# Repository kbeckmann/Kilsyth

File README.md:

# WIP! WIP! WIP! 
This repo is a work in progress and far from release-worthy. Please don't make your own boards and expect any kind of support. However, it might reach a stable point sometime in the future (as of 2019-01).

# Kilsyth: ECP5 FPGA + FT60x FIFO
Kilsyth is a piece of hardware that contains an FPGA (Lattice ECP5) and a SuperSpeed USB 3.0 FIFO-bridge (FT60x). The goal is to provide a platform to be able to transfer high speed data transfers between a PC and an FPGA. The FPGA in turn can do whatever - e.g. interface with SDR, video capture, act as a logic analyzer.

## Current status
It's still in the early bring-up phase. Initial verification shows that it actually seems to work.

### RevA
RevA is the first prototype and has been designed and built.

- [x] It doesn't smoke when powered up.
- [x] USB-C connector works but is messy to solder.
- [ ] Loopback test is almost in place. Using the proprietary driver, high bi-directional speeds are achieavable (> 98MB/s in both directions simultaneously). Just need to figure out some off-by-one errors...
- [ ] Bootloader to store a custom bitstream on the flash.

Errata:
- C9 is not a GPIO on ECP5 F12 and some other variants. To get the LED working put a jumper on pin 31 and 33 on the Wide connector.
- FT_CLK is not routed to a clock pin. Can be fixed with a bodge wire! Remove R50 and R36, swap their paths.
- JTAG connector has a funky footprint on the PCB because CCW vs Odd/Even pinout on the symbol vs footprint. But the PCB silk screen is accurate so don't worry - it's just a stupid pinout.
- Need to add pull-ups for the SPI flash.

### RevB
Ideas for RevB are still being collected. Feel free to suggest changes in an issue.

- Add support for reversible USB-C connector using [PI5USB30213A](https://www.diodes.com/products/connectivity-and-timing/switches-mux/protocol-switches/usb-switches/part/PI5USB30213A).

## Software usage (TODO)

Requires a patched migen and a patched ftdi library.. Nasty, I know, sorry.

```
Help:
$ python -m software.kilsyth -h

Run blinky:
$ python -m software.kilsyth run blinky

```

# Contact

Reach out to [@kbeckmann](https://twitter.com/kbeckmann) on Twitter or IRC/Freenode.

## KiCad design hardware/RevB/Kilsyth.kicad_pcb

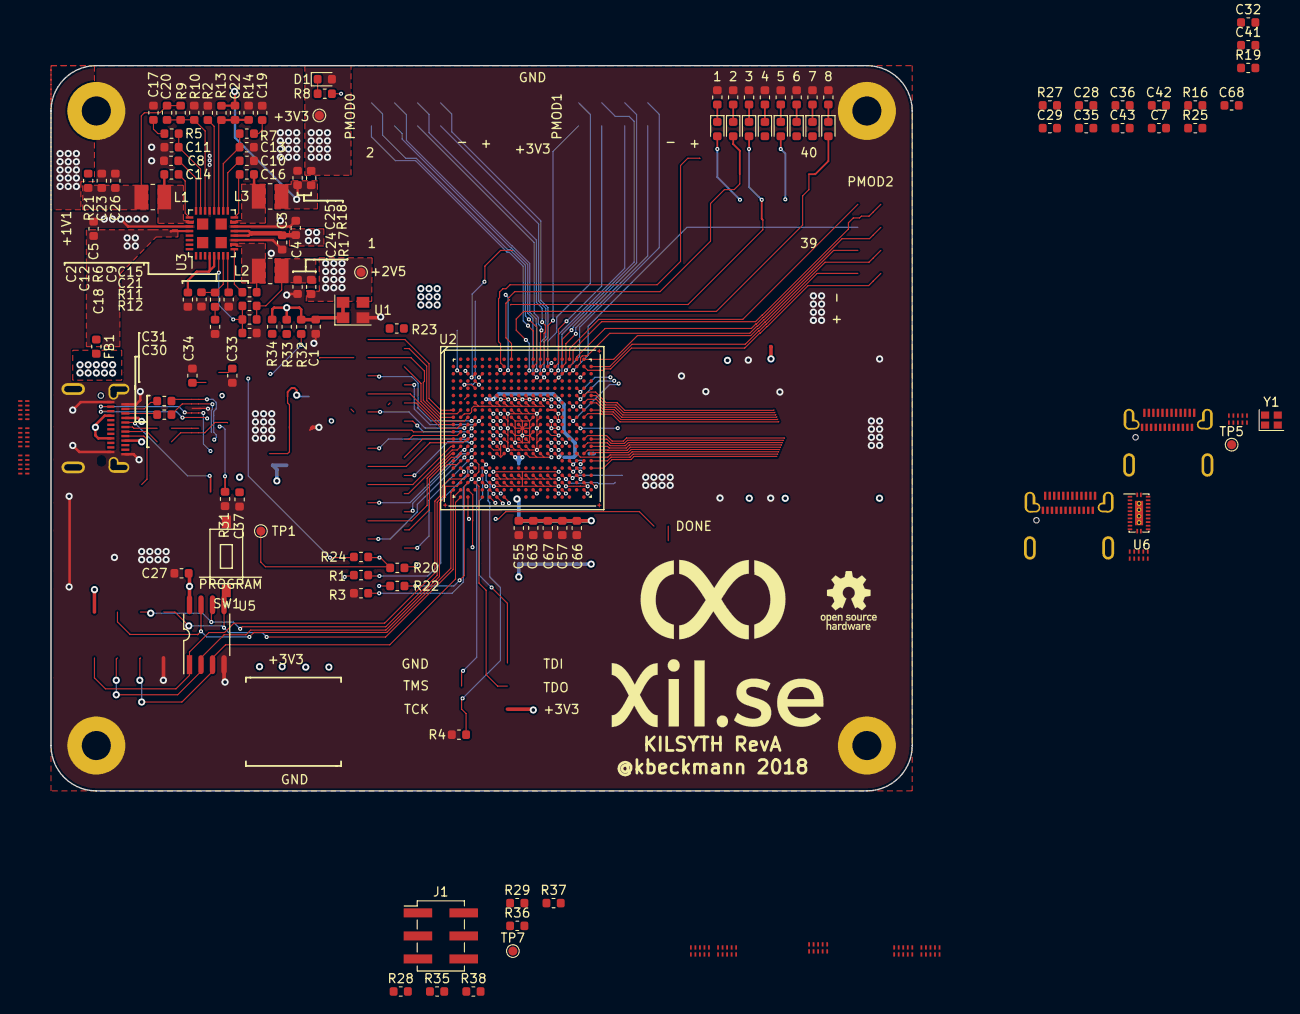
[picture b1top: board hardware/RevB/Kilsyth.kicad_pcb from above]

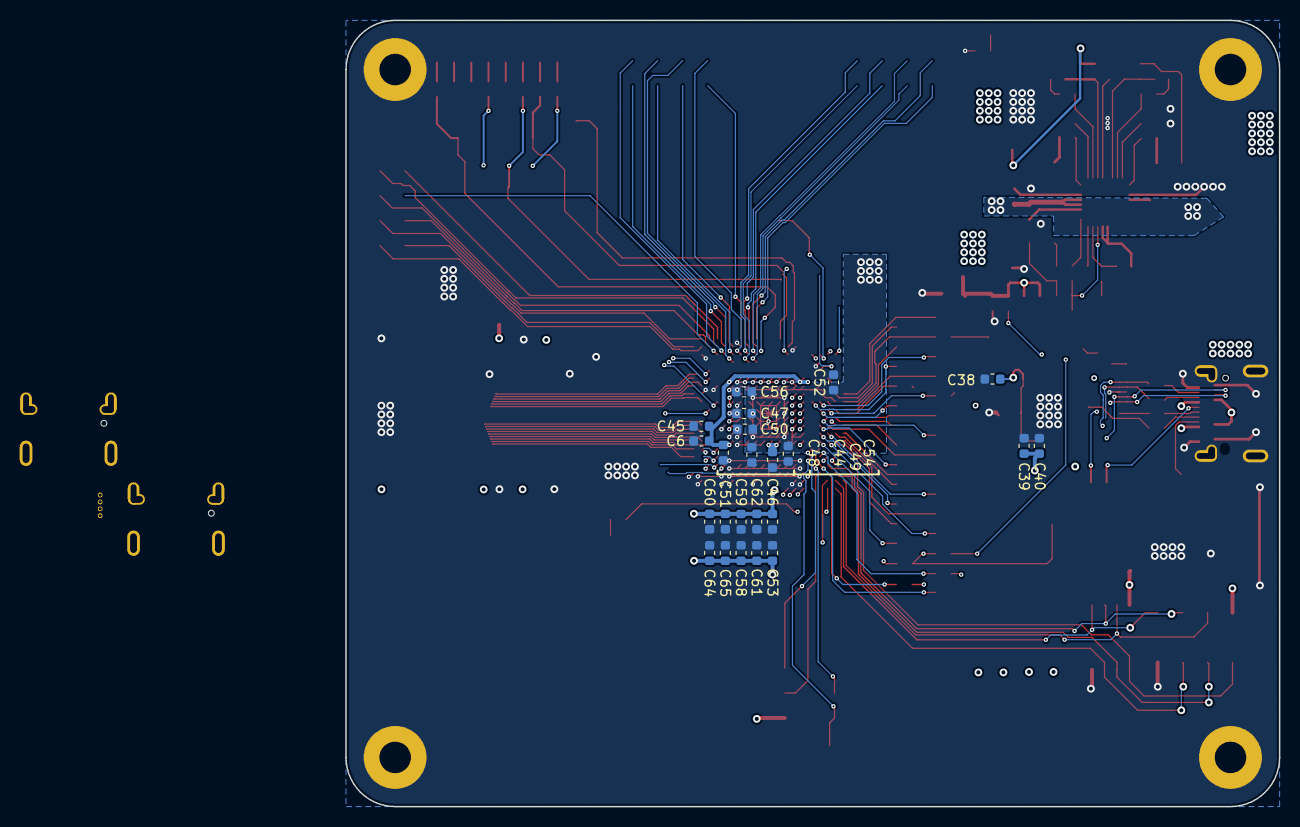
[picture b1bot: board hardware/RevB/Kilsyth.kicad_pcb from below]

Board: 4 copper layers, 95.0 x 80.0 mm, 154 parts (23 on the bottom side), 112 nets.

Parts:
C1, C6, C7, C27, C28, C29, C30, C31, C32, C35, C36, C37, C39, C40, C41, C42, C43, C44, C45, C46, C50, C51, C54, C55, C58, C60, C62, C64, C66, C68: 100n; C_0603_1608Metric
C2: 1u; C_0603_1608Metric
C3, C4, C5: 10u; C_0603_1608Metric
C8, C9, C10, C47, C48, C49, C52, C53, C56, C57, C59, C61, C63, C65, C67: 10n; C_0603_1608Metric
C11, C12, C13, C20, C21, C22: 22p; C_0603_1608Metric
C14, C15, C16: 47n; C_0603_1608Metric
C17, C18, C19: 3.3n; C_0603_1608Metric
C23, C24, C25, C26: 22u; C_0603_1608Metric
C33, C34: 18p; C_0603_1608Metric
C38: 4u7; C_0603_1608Metric
D1, D3, D4, D5, D6, D7, D8, D9, D10: LED; LED_0603_1608Metric
FB1: Ferrite_Bead; L_0603_1608Metric
H1, H2, H3, H4: MountingHole_3.2mm_M3_Pad
J1: Conn_JTAG; PinHeader_2x03_P2.54mm_Vertical_SMD
J2, J6, J7: DX07S024JJ2; USBC_DX07S024JJ2R1300
J3, J4, J5, J8, J9, J10, J11, J12, J13, J14: PUSB3FR4Z
L1, L2, L3: 2.2u; L_1008_1210
R1, R3, R12: 4.7K; R_0603_1608Metric
R2: 73.2K; R_0603_1608Metric
R4, R28: 4k7; R_0603_1608Metric
R5, R6, R7: 20K; R_0603_1608Metric
R8, R15, R26, R30, R59, R60, R61, R62, R63: 2K; R_0603_1608Metric
R9, R11, R13: 15K; R_0603_1608Metric
R10: 7K5; R_0603_1608Metric
R14: 3.3K; R_0603_1608Metric
R16, R27: 910K; R_0603_1608Metric
R17, R18, R21, R23, R24: 0R; R_0603_1608Metric
R19, R25: 2K2; R_0603_1608Metric
R20, R22, R32, R33, R34: 10K; R_0603_1608Metric
R29, R35, R37, R38: 10k; R_0603_1608Metric
R31: 1K6; R_0603_1608Metric
R36: 1k1; R_0603_1608Metric
SW1: SW_Push; SmallButton
TP1, TP2, TP3, TP5, TP7: TestPoint; TestPoint_Pad_D1.0mm
U1: DSC6001CI2A-016.0000T; Crystal_SMD_3225-4Pin_3.2x2.5mm
U2: LFE5UM-45F-6BG381C; BGA-381_pitch0.8mm_dia0.4mm
U3: TPS65261; S-PVQFN-N32
U5: IS25LP128F-JBLE; SOA008-150-208mil
U6: PI5USB30213A
Y1: 30MHz ±20ppm; Crystal_SMD_2016-4Pin_2.0x1.6mm

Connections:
+1V1: C44.1, C47.1, C50.1, C52.1, C54.1, C56.1, U2.H8, U2.H9, U2.H10, U2.H11, U2.H12, U2.H13, U2.J8, U2.J13, U2.K8, U2.K13, U2.L8, U2.L13, U2.M8, U2.M13, U2.N8, U2.N9, U2.N10, U2.N11, U2.N12, U2.N13
+1V8: R21.1, TP5.1
+2V5: C6.1, C45.1, C48.1, R17.1, TP2.1, U2.F6, U2.F15, U2.P6, U2.P15
+3V3: C1.1, C27.1, C39.1, C40.1, C46.1, C49.1, C51.1, C53.1, C55.1, C57.1, C58.1, C59.1, C60.1, C61.1, C62.1, C63.1, C64.1, C65.1, C66.1, C67.1, D1.2, J1.2, R1.1, R18.1, R19.2, R20.2, R22.2, R25.2, R28.1, R29.1, R32.2, R33.2, R34.2, R35.1, R36.1, R37.1, R38.1, TP3.1, U1.1, U1.4, U2.F9, U2.F10, U2.F11, U2.F12, U2.H6, U2.H7, U2.H14, U2.H15, U2.J6, U2.J15, U2.L6, U2.L7, U2.L14, U2.L15, U2.M6, U2.M15, U2.P9, U2.P10, U2.T2, U2.T3, U2.U2, U5.8
+5V: C3.1, C4.1, C5.1, J6.A4, J6.A9, J6.B4, J6.B9, J7.A4, J7.A9, J7.B4, J7.B9, U3.12, U3.13, U3.28, U3.29
/CC1: J2.A5, J4.5, J4.6, U6.11
/CC2: J2.B5, J4.4, J4.7, U6.12
/FLASH_CSn: R28.2, U2.R2, U5.1
/FLASH_HOLDn: R29.2, U2.W1, U5.7
/FLASH_MISO: R38.2, U2.V2, U5.2
/FLASH_MOSI: R37.2, U2.W2, U5.5
/FLASH_SCK: R36.2, U2.U3, U5.6
/FLASH_WPn: R35.2, U2.Y2, U5.3
/HDRX0_D0CH0_N: J6.B10, J8.5, J8.6, U2.Y6
/HDRX0_D0CH0_P: J6.B11, J8.4, J8.7, U2.Y5
/HDRX0_D0CH1_N: J6.A10, J9.5, J9.6, U2.Y8
/HDRX0_D0CH1_P: J6.A11, J9.4, J9.7, U2.Y7
/HDRX0_D1CH0_N: J7.B10, J11.5, J11.6, U2.Y15
/HDRX0_D1CH0_P: J7.B11, J11.4, J11.7, U2.Y14
/HDRX0_D1CH1_N: J7.A10, J12.5, J12.6, U2.Y17
/HDRX0_D1CH1_P: J7.A11, J12.4, J12.7, U2.Y16
/HDTX0_D0CH0_N: C29.2, J8.2, J8.9, U2.W5
/HDTX0_D0CH0_P: C32.2, J8.1, J8.10, U2.W4
/HDTX0_D0CH1_N: C35.2, J9.2, J9.9, U2.W9
/HDTX0_D0CH1_P: C36.2, J9.1, J9.10, U2.W8
/HDTX0_D1CH0_N: C41.2, J11.2, J11.9, U2.W14
/HDTX0_D1CH0_P: C42.2, J11.1, J11.10, U2.W13
/HDTX0_D1CH1_N: C43.2, J12.2, J12.9, U2.W18
/HDTX0_D1CH1_P: C68.2, J12.1, J12.10, U2.W17
/INITn: R22.1, U2.V3
/JTAG_TCK: J1.4, R4.1, U2.T5
/JTAG_TDI: J1.3, U2.R5
/JTAG_TDO: J1.6, U2.V4
/JTAG_TMS: J1.5, U2.U5
/REFCLK_D0_N: J6.B8, J10.4, J10.7, U2.Y12
/REFCLK_D0_P: J6.A8, J10.5, J10.6, U2.Y11
/REFCLK_D1_N: J7.B8, J10.1, J10.10, U2.W20
/REFCLK_D1_P: J7.A8, J10.2, J10.9, U2.Y19
/RX1+: J2.B11, J3.5, J3.6, U6.14
/RX1-: J2.B10, J3.4, J3.7, U6.15
/RX2+: J2.A11, J5.4, J5.7, U6.19
/RX2-: J2.A10, J5.5, J5.6, U6.18
/TX1+: C31.1, J2.A2, J3.2, J3.9
/TX1-: C30.1, J2.A3, J3.1, J3.10
/TX2+: C28.1, J2.B2, J5.1, J5.10
/TX2-: C7.1, J2.B3, J5.2, J5.9
/USBC0_CC1: J6.A5, J13.5, J13.6
/USBC0_CC2: J6.B5, J13.4, J13.7
/USBC0_USB_N: J6.A7, J6.B7, J13.2, J13.9
/USBC0_USB_P: J6.A6, J6.B6, J13.1, J13.10
/USBC1_CC1: J7.A5, J14.5, J14.6
/USBC1_CC2: J7.B5, J14.4, J14.7
/USBC1_USB_N: J7.A7, J7.B7, J14.2, J14.9
/USBC1_USB_P: J7.A6, J7.B6, J14.1, J14.10
/USB_D+: J2.A6, J2.B6, J4.2, J4.9
/USB_D-: J2.A7, J2.B7, J4.1, J4.10
FT_GPIO0: R20.1, R24.2, R25.1, SW1.2, TP1.1, U2.W3
FT_GPIO1: R19.1, R23.2
GND: C1.2, C2.2, C3.2, C4.2, C5.2, C6.2, C8.2, C9.2, C10.2, C11.2, C12.2, C13.2, C17.2, C18.2, C19.2, C23.2, C24.2, C25.2, C26.2, C27.2, C33.1, C34.1, C37.2, C38.2, C39.2, C40.2, C44.2, C45.2, C46.2, C47.2, C48.2, C49.2, C50.2, C51.2, C52.2, C53.2, C54.2, C55.2, C56.2, C57.2, C58.2, C59.2, C60.2, C61.2, C62.2, C63.2, C64.2, C65.2, C66.2, C67.2, H1.1, H2.1, H3.1, H4.1, J1.1, J2.A1, J2.A12, J2.B1, J2.B12, J2.S1, J3.3, J3.8, J4.3, J4.8, J5.3, J5.8, J6.A1, J6.A12, J6.B1, J6.B12, J6.S1, J7.A1, J7.A12, J7.B1, J7.B12, J7.S1, J8.3, J8.8, J9.3, J9.8, J10.3, J10.8, J11.3, J11.8, J12.3, J12.8, J13.3, J13.8, J14.3, J14.8, R2.2, R3.1, R4.2, R8.2, R10.2, R12.2, R14.2, R15.2, R26.2, R30.2, R31.2, R59.2, R60.2, R61.2, R62.2, R63.2, SW1.1, U1.2, U2.B7, U2.B14, U2.C19, U2.D4, U2.F7, U2.F8, U2.F13, U2.F14, U2.G4, U2.G6, U2.G7, U2.G8, U2.G9, U2.G10, U2.G11, U2.G12, U2.G13, U2.G14, U2.G15, U2.G17, U2.H19, U2.J2, U2.J7, U2.J9, U2.J10, U2.J11, U2.J12, U2.J14, U2.K6, U2.K7, U2.K9, U2.K10, U2.K11, U2.K12, U2.K14, U2.K15, U2.L9, U2.L10, U2.L11, U2.L12, U2.M2, U2.M7, U2.M9, U2.M10, U2.M11, U2.M12, U2.M14, U2.M16, U2.N6, U2.N7, U2.N14, U2.N15, U2.P7, U2.P8, U2.P11, U2.P12, U2.P13, U2.P14, U2.R19, U2.U7, U2.U8, U2.U9, U2.U10, U2.U11, U2.U12, U2.U13, U2.U14, U2.V5, U2.V6, U2.V7, U2.V8, U2.V9, U2.V12, U2.V13, U2.V14, U2.V15, U2.V16, U2.V19, U2.V20, U2.W6, U2.W7, U2.W12, U2.W15, U2.W16, U2.W19, U3.11, U3.14, U3.21, U3.27, U5.4, U6.3, U6.13, U6.PAD
unnamed: C2.1, U3.4, U3.5
unnamed: C7.2, U6.20
unnamed: C8.1, U3.24
unnamed: C9.1, U3.8
unnamed: C10.1, U3.17
unnamed: C11.1, R5.1, U3.23
unnamed: C12.1, R6.1, U3.7
unnamed: C13.1, R7.1, U3.18
unnamed: C14.1, U3.25
unnamed: C14.2, L1.1, U3.26
unnamed: C15.1, U3.9
unnamed: C15.2, L2.1, U3.10
unnamed: C16.1, U3.16
unnamed: C16.2, L3.1, U3.15
unnamed: C17.1, R5.2
unnamed: C18.1, R6.2
unnamed: C19.1, R7.2
unnamed: C20.1, C23.1, C26.1, L1.2, R9.1, R21.2
unnamed: C20.2, R9.2, R10.1, U3.22
unnamed: C21.1, C24.1, L2.2, R11.1, R17.2
unnamed: C21.2, R11.2, R12.1, U3.6
unnamed: C22.1, C25.1, L3.2, R13.1, R18.2
unnamed: C22.2, R13.2, R14.1, U3.19
unnamed: C28.2, U6.21
unnamed: C29.1, J6.A3
unnamed: C30.2, U6.17
unnamed: C31.2, U6.16
unnamed: C32.1, J6.A2
unnamed: C33.2, Y1.1
unnamed: C34.2, Y1.3
unnamed: C35.1, J6.B3
unnamed: C36.1, J6.B2
unnamed: C41.1, J7.A3
unnamed: C42.1, J7.A2
unnamed: C43.1, J7.B3
unnamed: C68.1, J7.B2
unnamed: D1.1, R8.1
unnamed: D3.1, R15.1
unnamed: D4.1, R26.1
unnamed: D5.1, R30.1
unnamed: D6.1, R59.1
unnamed: D7.1, R60.1
unnamed: D8.1, R61.1
unnamed: D9.1, R62.1
unnamed: D10.1, R63.1
unnamed: FB1.2, J2.A4, J2.A9, J2.B4, J2.B9
unnamed: R1.2, U2.T4
unnamed: R2.1, U3.20
unnamed: R3.2, U2.R4, U2.U4
unnamed: R16.2, U6.23
unnamed: TP7.1, U2.Y3
VBUS: FB1.1, R16.1, R27.2, U6.6
VD10: C37.1, C38.1

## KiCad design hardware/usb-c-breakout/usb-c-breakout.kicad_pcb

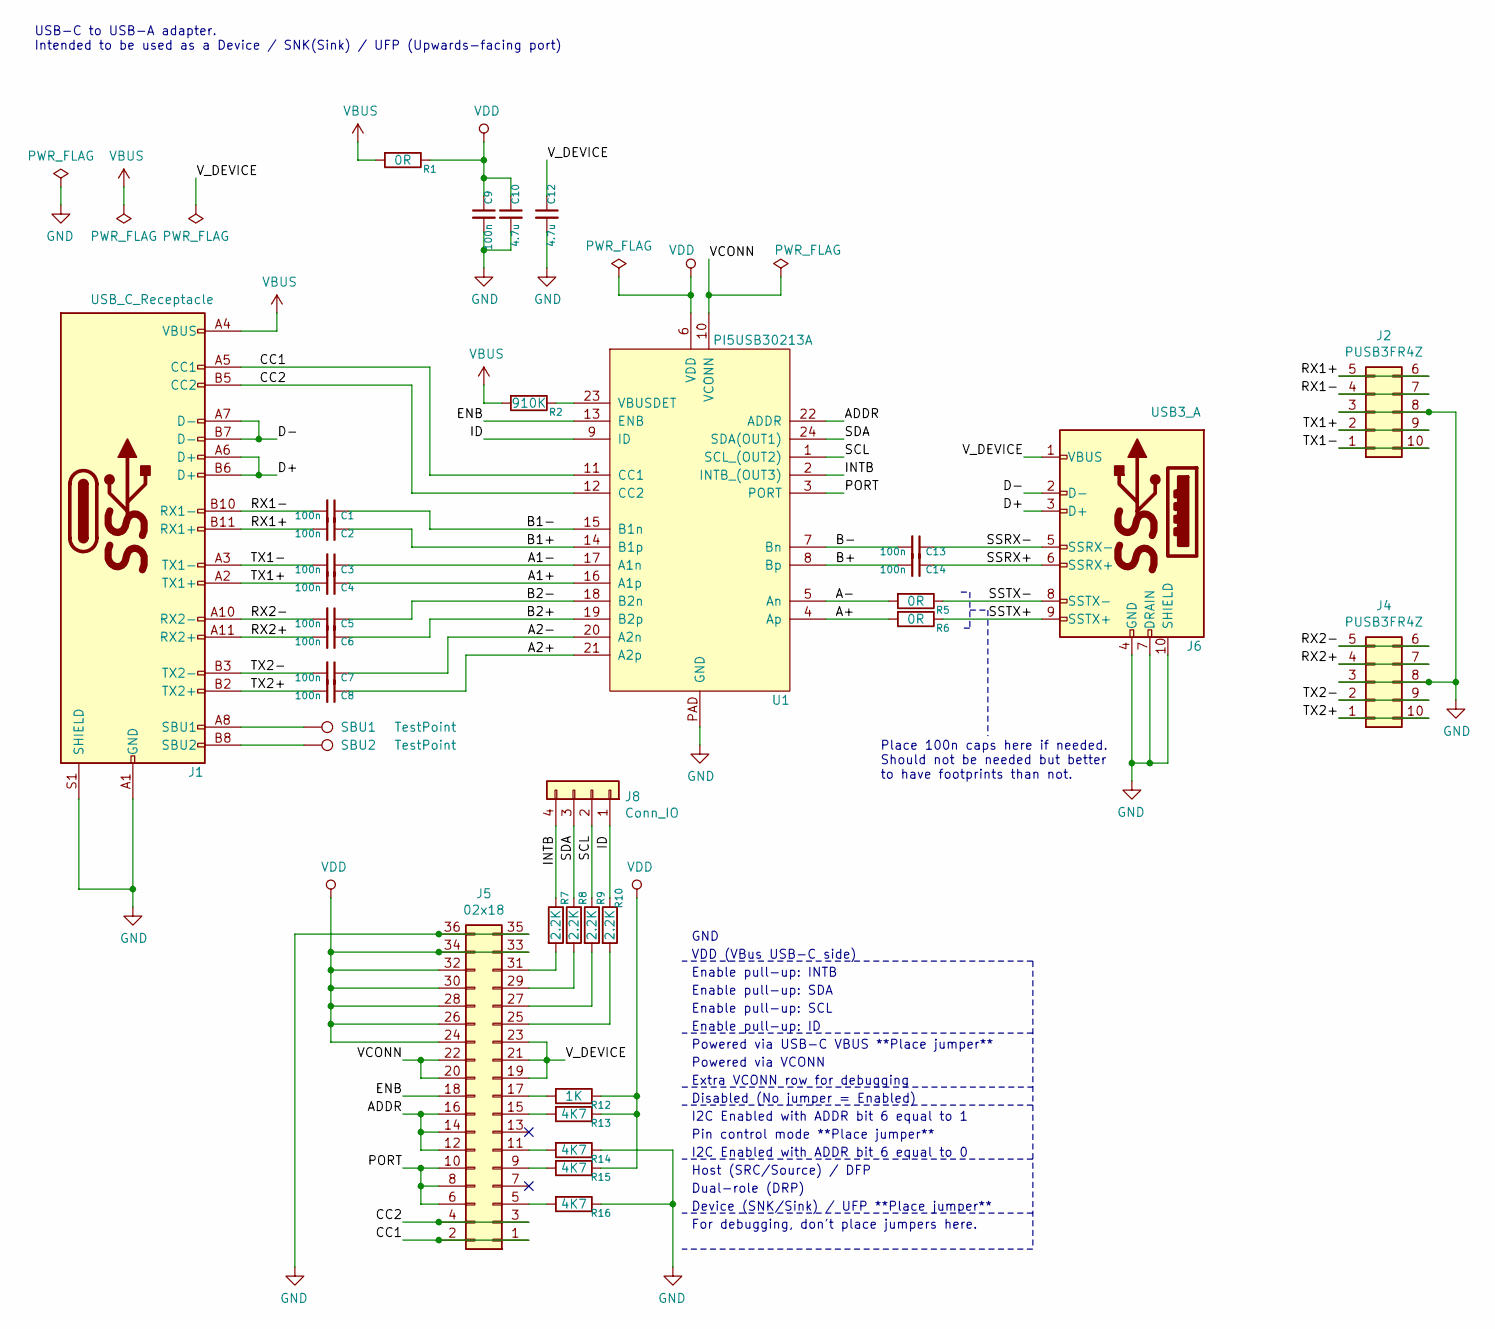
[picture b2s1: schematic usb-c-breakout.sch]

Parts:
C1, C2, C3, C4, C5, C6, C7, C8, C9, C13, C14: 100n; C_0402_1005Metric
C10, C12: 4.7u; C_0603_1608Metric
J1: USB_C_Receptacle; USB_C_Receptacle_CUI_UJ31-CH-31-SMT-TR
J2, J4: PUSB3FR4Z; Mouser 771-PUSB3FR4Z
J5: 02x18; PinHeader_2x18_P2.54mm_Vertical
J6: USB3_A; USB3_A_Female_Vertical
J8: Conn_IO; PinHeader_1x04_P2.54mm_Vertical
R1: 0R; R_0603_1608Metric
R2: 910K; R_0402_1005Metric
R5, R6: 0R; R_0402_1005Metric
R7, R8, R9, R10: 2.2K; R_0402_1005Metric
R12: 1K; R_0402_1005Metric
R13, R14, R15, R16: 4K7; R_0402_1005Metric
SBU1, SBU2: TestPoint; TestPoint_Pad_D1.0mm
U1: PI5USB30213A; Mouser PI5USB30213AXEAEX

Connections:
/A1+: C4.1, U1.16 (A1p)
/A1-: C3.1, U1.17 (A1n)
/A2+: C8.1, U1.21 (A2p)
/A2-: C7.1, U1.20 (A2n)
/A+: R6.2, U1.4 (Ap)
/A-: R5.2, U1.5 (An)
/ADDR: J5.12, J5.14, J5.16, U1.22 (ADDR)
/B1+: C2.1, U1.14 (B1p)
/B1-: C1.1, U1.15 (B1n)
/B2+: C6.1, U1.19 (B2p)
/B2-: C5.1, U1.18 (B2n)
/B+: C14.2, U1.8 (Bp)
/B-: C13.2, U1.7 (Bn)
/CC1: J1.A5 (CC1), J5.1, J5.2, U1.11 (CC1)
/CC2: J1.B5 (CC2), J5.3, J5.4, U1.12 (CC2)
/D+: J1.A6 (D+), J1.B6 (D+), J6.3 (D+)
/D-: J1.A7 (D-), J1.B7 (D-), J6.2 (D-)
/ENB: J5.18, U1.13 (ENB)
/ID: J8.1, R10.1, U1.9 (ID)
/INTB: J8.4, R7.1, U1.2 (INTB_(OUT3))
/PORT: J5.6, J5.8, J5.10, U1.3 (PORT)
/RX1+: C2.2, J1.B11 (RX1+), J2.5, J2.6
/RX1-: C1.2, J1.B10 (RX1-), J2.4, J2.7
/RX2+: C6.2, J1.A11 (RX2+), J4.4, J4.7
/RX2-: C5.2, J1.A10 (RX2-), J4.5, J4.6
/SCL: J8.2, R9.1, U1.1 (SCL_(OUT2))
/SDA: J8.3, R8.1, U1.24 (SDA(OUT1))
/SSRX+: C14.1, J6.6 (SSRX+)
/SSRX-: C13.1, J6.5 (SSRX-)
/SSTX+: J6.9 (SSTX+), R6.1
/SSTX-: J6.8 (SSTX-), R5.1
/TX1+: C4.2, J1.A2 (TX1+), J2.2, J2.9
/TX1-: C3.2, J1.A3 (TX1-), J2.1, J2.10
/TX2+: C8.2, J1.B2 (TX2+), J4.1, J4.10
/TX2-: C7.2, J1.B3 (TX2-), J4.2, J4.9
/VCONN: J5.20, J5.22, U1.10 (VCONN)
/V_DEVICE: C12.1, J5.19, J5.21, J5.23, J6.1 (VBUS)
GND: C9.2, C10.2, C12.2, J1.A1 (GND), J1.A12 (GND), J1.B1 (GND), J1.B12 (GND), J1.S1 (SHIELD), J2.3, J2.8, J4.3, J4.8, J5.35, J5.36, J6.4 (GND), J6.7 (DRAIN), J6.10 (SHIELD), R14.1, R16.1, U1.PAD (GND)
unnamed: J1.A8 (SBU1), SBU1.1
unnamed: J1.B8 (SBU2), SBU2.1
unnamed: J5.5, R16.2
unnamed: J5.9, R15.2
unnamed: J5.11, R14.2
unnamed: J5.15, R13.2
unnamed: J5.17, R12.2
unnamed: J5.25, R10.2
unnamed: J5.27, R9.2
unnamed: J5.29, R8.2
unnamed: J5.31, R7.2
unnamed: R2.1, U1.23 (VBUSDET)
VBUS: J1.A4 (VBUS), J1.A9 (VBUS), J1.B4 (VBUS), J1.B9 (VBUS), R1.2, R2.2
VDD: C9.1, C10.1, J5.24, J5.26, J5.28, J5.30, J5.32, J5.33, J5.34, R1.1, R12.1, R13.1, R15.1, U1.6 (VDD)

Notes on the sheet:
USB-C to USB-A adapter. Intended to be used as a Device / SNK(Sink) / UFP (Upwards-facing port)
Place 100n caps here if needed. Should not be needed but better to have footprints than not.
Extra VCONN row for debugging
For debugging, don't place jumpers here.
Powered via VCONN
Powered via USB-C VBUS **Place jumper**
Device (SNK/Sink) / UFP **Place jumper**
Dual-role (DRP)
Host (SRC/Source) / DFP
I2C Enabled with ADDR bit 6 equal to 0
Pin control mode **Place jumper**
I2C Enabled with ADDR bit 6 equal to 1
Disabled (No jumper = Enabled)
Enable pull-up: ID
Enable pull-up: SCL
Enable pull-up: SDA
Enable pull-up: INTB
VDD (VBus USB-C side)
GND

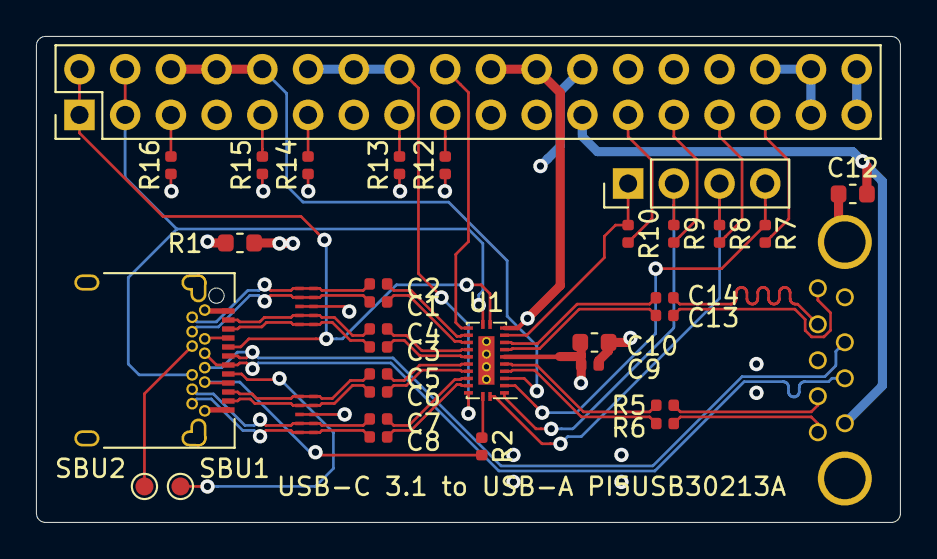
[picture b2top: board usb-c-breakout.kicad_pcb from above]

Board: 4 copper layers, 48.0 x 27.0 mm, 35 parts (0 on the bottom side), 52 nets.
